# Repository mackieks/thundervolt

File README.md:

<picture> <source media="(prefers-color-scheme: dark)" srcset="images/thundervolt_logo_white.png">  </picture> 

Thundervolt is a suite of open-source hardware and software that enables software-configurable undervolting of 4-layer Wiis. 

The Thundervolt PCBs (Thundervolt 1 and Thundervolt Lite shown) are stylish, highly-integrated power hats for 4-layer Wiis that solder directly to the Wii motherboard. Only 3 wires are necessary to connect Thundervolt to the Wii (I2C and Reset). Power is supplied via two additional wires.

The Thundervolt homebrew app (Dolphin debug version shown) provides granular control over each voltage regulator on the Thundervolt board, as well as emergency overtemperature protection with a configurable threshold. 

Users can apply changes live, and save settings to Thundervolt's EEPROM for persistence across reboots. 

More functionality such as CPU/GPU/MEM stress tests and a power monitor for Thundervolt 2 will be added to the app in the future.

## Features
- 0.8mm 4L rigid PCB — solders directly to 4-layer Wii motherboards
- 55 x 47mm — fits within all but the most extreme trim outlines
- 2.4V to 5.5V input (intended for 1S li-ion or 5V USB-C)
- Highly efficient I2C-controlled buck regulators for 1V, 1.15V, and 1.8V (η > 90%)
- Highly efficient I2C-controlled buck-boost regulator for 3.3V (η > 90%)
- Dynamic undervolting, configurable via Wii homebrew app
- Safe mode solder jumper to force stock voltages
- Wii power-on reset functionality (aka U10 emulation)
- Onboard TMP1075N for temperature monitoring and emergency overtemp shutdown
- Integrated INA700s for realtime voltage/current/power monitoring (Thundervolt 2 only)

## What Thundervolt does NOT do
- Battery management and charging
- Fan control
- Power button handling for portables
- USB PD negotiation

Adding a full BMS to Thundervolt would require major sacrifices to regulator efficiency, thermal performance, and cost. A companion board called *Mjolnir* is in development to fulfill these needs, and will feature tight integration with the existing Thundervolt ecosystem.

## Ordering & Assembly

See [the hardware folder](https://github.com/mackieks/thundervolt/tree/main/hardware) for details on ordering and [assembling](https://github.com/mackieks/thundervolt/blob/main/hardware/ASSEMBLY.md) Thundervolt PCBs.

## Usage
The homebrew app is pretty self explanatory; see [the demo on YouTube](https://youtu.be/DeZFMLoE9EQ) for details. A full writeup will come later.

## Credits

Thundervolt hardware designed by YveltalGriffin

Thundervolt firmware by loopj

Thundervolt homebrew by:
- YveltalGriffin (UI, app)
- loopj (I2C, app)
- Alex/supertazon (graphics)
- ShockSlayer (music)

## License

Thundervolt hardware is licensed under Solderpad Hardware License v2.1.

Thundervolt software (firmware + homebrew) is provided under The MIT License.

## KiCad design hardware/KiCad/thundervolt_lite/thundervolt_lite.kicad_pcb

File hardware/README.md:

<picture> <source media="(prefers-color-scheme: dark)" srcset="../images/thundervolt_logo_white.png">  </picture> 

There are 3 variants of the Thundervolt PCB. As of 2024-07-07, **Thundervolt Lite** and **Thundervolt 1** have been released.
- **Thundervolt Lite**
  - A low cost revision of the original design with **identical functionality** to Thundervolt 1. It does not require VIPPO and only costs $7 for 10 bare boards!
  - Thundervolt Lite is easier to assemble and easier to solder to the Wii motherboard.
  - Fully tested and released to the public! This folder contains the KiCAD source and Gerbers.
- **Thundervolt 1**
  - The original design, with software-controlled undervolting and temperature sensing. It requires a [VIPPO/POFV PCB](https://jlcpcb.com/blog/32-Free-Via-in-Pad-on-6-20-Layer-PCBs-with-POFV) which is rather expensive ($10 per bare board).
  - Fully tested and released to the public! This folder contains the KiCAD source and Gerbers.
- **Thundervolt 2**
  - The Lamborghini of Wii voltage regulation. Thundervolt 2 includes four INA700 power monitor ICs and can report the Wii's current and power consumption in real time. It requires an even higher spec PCB than Thundervolt 1 and is quite expensive ($14-$20 per bare board)
  - Currently unreleased — still in testing

- All Thundervolt revisions require placing and reflowing at least one chipscale BGA (the TPS63810 3.3V buck-boost regulator). 
- Thundervolt 1 and 2 require placing and reflowing an additional chipscale part (LP5907UVX-1.8, 0.7x0.7mm) and have tighter component spacing than Lite. 
- Thundervolt 2 also requires placing four additional chipscale BGAs (INA700, 1.2x1.3mm)
- Thundervolt Lite is the easiest to assemble. Thundervolt 1 is tougher, and Thundervolt 2 is the most challenging. Magnification is highly recommended for assembling all variants.

Two jig PCBs for solderpaste stenciling are also provided. Order both jigs as 2-layer 0.8mm boards.

## Ordering PCBs

### Thundervolt Lite

Recommended board fabrication specs for **Thundervolt Lite** (JLCPCB).

**MANDATORY**
- 0.8mm 4-layer rigid PCB
- Tented or plugged vias
- Min via hole size/diameter: leave at default. Thundervolt Lite has large vias that do not incur additional charges.

Optional
- ENIG (improves solderability for chipscale BGAs)
- 1oz/in² copper on internal layers - not necessary, but technically improves PDN performance (imperceptible to end user)
- Black soldermask - not necessary, but looks great with the lightning bolt art :)

In the **Remark** section of your Thundervolt Lite PCB order, paste the following comment:
```
Kindly note that the graphics on the fMask layer are for aesthetics. Please do NOT edit any of the fMask apertures on the board, or remove any thin soldermask webs. Thank you!
```

If JLC tries to upcharge you for the soldermask artwork, push back. The artwork requires zero additional work or intervention on their part. Feel free to reference my Thundervolt Lite order number if necessary: **Y118-2549677A**

### Thundervolt 1

Recommended board fabrication specs for **Thundervolt 1** (JLCPCB). Thundervolt 1 is a high-spec PCB. Please read this entire section so you understand the fab requirements. 

**MANDATORY**
- 0.8mm 4-layer rigid PCB
- Epoxy Filled & Capped vias (aka VIPPO or POFV)
- Min via hole size/diameter: 0.15mm/(0.25/0.3mm)

Optional
- ENIG (improves solderability for chipscale BGAs)
- 1oz/in² copper on internal layers - not necessary, but technically improves PDN performance (imperceptible to end user)
- Black soldermask - not necessary, but looks great with the lightning bolt art :)

In the **Remark** section of your Thundervolt 1 PCB order, paste the following comment:
```
Kindly note that the graphics on the fMask layer are for aesthetics. Please do NOT edit any of the fMask apertures on the board, or remove any thin soldermask webs. Thank you!
```

If JLC tries to upcharge you for the soldermask artwork, push back. The artwork requires zero additional work or intervention on their part. Feel free to reference my Thundervolt 1 order number if necessary: **Y108-2549677A**

**Note:** Check the box for **Confirm Production File**. Then check the box for "Do Not Confirm Automatically." JLCPCB will often edit the gerbers in unpleasant ways and you **must** push back on this. If they change the via drill sizes, you need to request that they abide by their listed spec of 0.15mm drills. 

A comment like this when reviewing the production file goes a long way:
```
In the production file, the via drill size has been changed from 0.15mm to 0.2mm [or whatever they changed it to]. Please do not change the via size. They should be 0.15mm drill and 0.3mm diameter as in the original file. I greatly appreciate your assistance with this. Thanks!
```

Some amount of "compensation" (growth of annular rings + padshaving) is unavoidable; however, if the drills are increased to 0.2mm or more, this will result in extreme padshaving of many vias/traces. You'll also notice that they expand the copper clearance around drills on inner layers as part of the compensation process. As long as they are not changing the drill diameters, this is OK. They may also request to remove annular rings ("pads") on internal layers. This is OK as it lessens the impact of their copper clearance expansion on the inner planes.

## Stencil and Jig

Both an electropolished solder paste stencil and the two jig PCBs (jig1, jig2) are **highly** recommended for assembly. 

**MANDATORY STENCIL SPECS**
- Custom dimensions: **90 x 90mm**
- Top only
- Electropolishing

Order both jig1 and jig2 as 0.8mm 2-layer PCBs. In the **Remark** section of both jig PCB orders, paste the following comment:
```
Please note that this is a mechanical PCB and does not contain any drill holes or soldermask openings. Thank you!
```

## BOM

**Thundervolt Lite:** [Link to Mouser cart with BOM](https://www.mouser.com/ProjectManager/ProjectDetail.aspx?AccessID=3CC491924A) [Link to Digikey cart with BOM](https://www.digikey.com/en/mylists/list/P9BJON8540)

**Thundervolt 1**: [Link to Mouser cart with BOM](https://www.mouser.com/ProjectManager/ProjectDetail.aspx?AccessID=D2F0182832)

**Note:** The 0412CDMCCDS-R22MC low-profile inductors used on Thundervolt Lite are only available [from Digikey.](https://www.digikey.com/en/products/detail/sumida-america-inc/0412CDMCCDS-R22MC/11682034)

**Note:** The XFL5015-221MEC low-profile inductors used on Thundervolt 1 and Thundervolt 2 are only available [directly from Coilcraft.](https://www.coilcraft.com/en-us/products/power/shielded-inductors/molded-inductor/xfl/xfl501x/xfl5015-221/)

## Assembly

See [ASSEMBLY.md](https://github.com/mackieks/thundervolt/blob/main/hardware/ASSEMBLY.md) for assembly instructions.

## License

Thundervolt hardware was designed by YveltalGriffin and is licensed under Solderpad Hardware License v2.1.

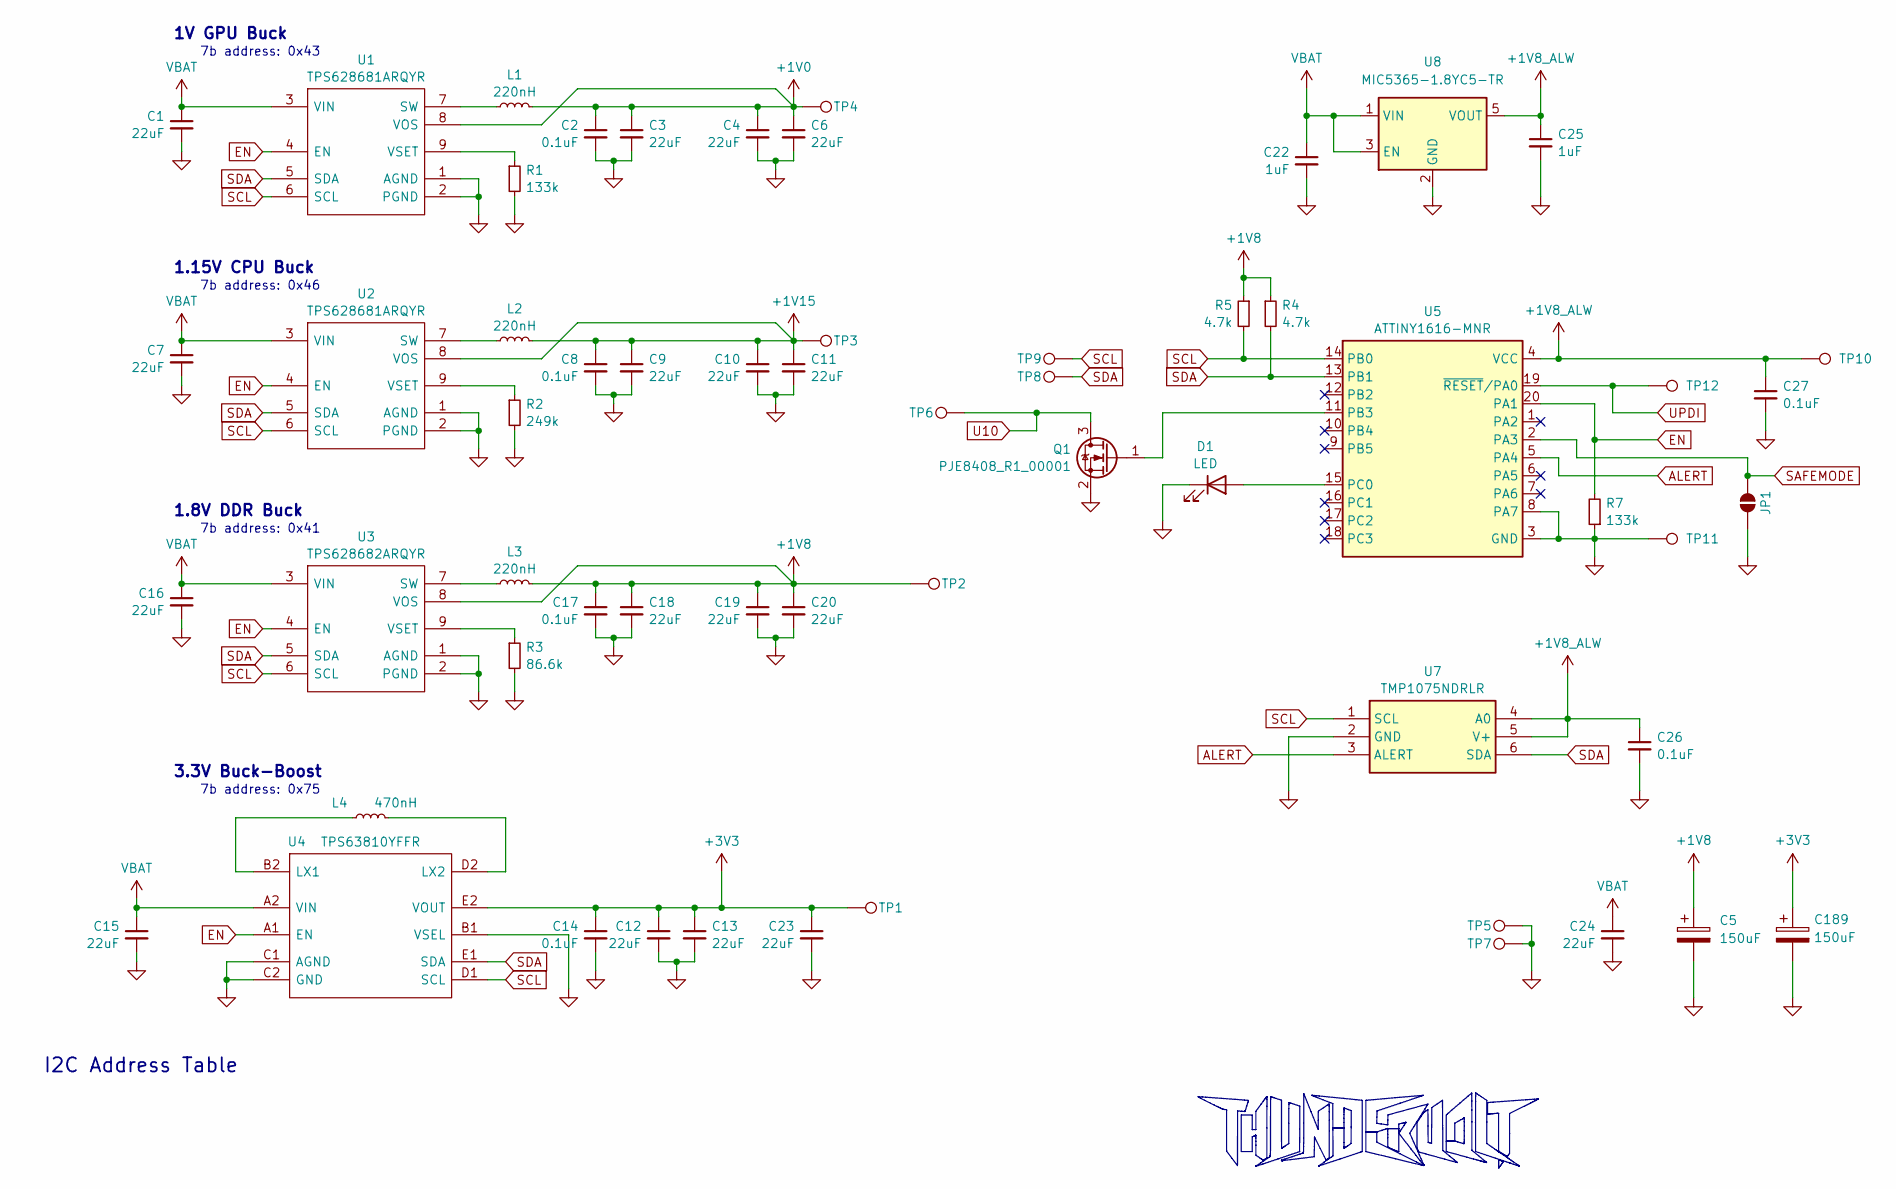
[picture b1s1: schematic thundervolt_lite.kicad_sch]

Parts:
C1, C3, C4, C6, C7, C9, C10, C11, C12, C13, C15, C16, C18, C19, C20, C23, C24: 22uF; C_0603_1608Metric
C2, C8, C14, C17, C26, C27: 0.1uF; C_0402_1005Metric
C5, C189: 150uF; CP_EIA-3528-15_AVX-H
C22, C25: 1uF; C_0402_1005Metric
D1: LED; LED_0603_1608Metric
JP1: SolderJumper_2_Open; SolderJumper-2_P1.3mm_Open_RoundedPad1.0x1.5mm
L1, L2: 220nH; 0412CDMCCDS-R22MC
L3: 220nH; INDC3225X120N
L4: 470nH; L_0805_2012Metric
Q1: PJE8408_R1_00001; SOT-523
R1, R7: 133k; R_0402_1005Metric
R2: 249k; R_0402_1005Metric
R3: 86.6k; R_0402_1005Metric
R4, R5: 4.7k; R_0402_1005Metric
TP1: 3V3; TestPoint_Pad_1.5x1.0mm
TP2: 1V8; TestPoint_Pad_3x1.0mm
TP3: 1V15; TestPoint_Pad_3x1.0mm
TP4: 1V0; TestPoint_Pad_3x1.0mm
TP5, TP7: GND; TestPoint_Pad_3x1.0mm
TP6, TP8: SDA; TestPoint_Pad_D1.0mm
TP9: SCL; TestPoint_Pad_D1.0mm
TP10: VBAT; TestPoint_Pad_D1.0mm
TP11: GND; TestPoint_Pad_D1.0mm
TP12: UPDI; TestPoint_Pad_D1.0mm
U1, U2: TPS628681ARQYR; TPS628680ARQYR; Mouser Part Number 595-TPS628680ARQYR
U3: TPS628682ARQYR; TPS628680ARQYR; Mouser Part Number 595-TPS628680ARQYR
U4: TPS63810YFFR; BGA15C40P3X5_134X226X62; Mouser Part Number 595-TPS63810YFFR
U5: ATTINY1616-MNR; VQFN-20-1EP_3x3mm_P0.4mm_EP1.7x1.7mm
U7: TMP1075NDRLR; SOTFL50P160X60-6N; Mouser Part Number 595-TMP1075NDRLR
U8: MIC5365-1.8YC5-TR; SOT-353_SC-70-5

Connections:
+1V0: C2.1, C3.1, C4.1, C6.1, L1.2, TP4.1, U1.8 (VOS)
+1V8: C5.1, C17.1, C18.1, C19.1, C20.1, L3.2, R4.1, R5.1, TP2.1, U3.8 (VOS)
+1V8_ALW: C25.1, C26.1, C27.1, TP10.1, U5.4 (VCC), U7.4 (A0), U7.5 (V+), U8.5 (VOUT)
+1V15: C8.1, C9.1, C10.1, C11.1, L2.2, TP3.1, U2.8 (VOS)
+3V3: C12.1, C13.1, C14.1, C23.1, C189.1, TP1.1, U4.E2 (VOUT), U4.E3 (VOUT_2)
ALERT: U5.5 (PA4), U7.3 (ALERT)
EN: R7.2, U1.4 (EN), U2.4 (EN), U3.4 (EN), U4.A1 (EN), U5.20 (PA1)
GND: C1.2, C2.2, C3.2, C4.2, C5.2, C6.2, C7.2, C8.2, C9.2, C10.2, C11.2, C12.2, C13.2, C14.2, C15.2, C16.2, C17.2, C18.2, C19.2, C20.2, C22.2, C23.2, C24.2, C25.2, C26.2, C27.2, C189.2, D1.1 (K), JP1.1 (A), Q1.2 (S), R1.2, R2.2, R3.2, R7.1, TP5.1, TP7.1, TP11.1, U1.1 (AGND), U1.2 (PGND), U2.1 (AGND), U2.2 (PGND), U3.1 (AGND), U3.2 (PGND), U4.B1 (VSEL), U4.C1 (AGND), U4.C2 (GND), U4.C3 (GND_2), U5.3 (GND), U5.8 (PA7), U5.21 (GND), U7.2 (GND), U8.2 (GND)
unnamed: D1.2 (A), U5.15 (PC0)
unnamed: Q1.1 (G), U5.11 (PB3)
unnamed: L1.1, U1.7 (SW)
unnamed: R1.1, U1.9 (VSET)
unnamed: L2.1, U2.7 (SW)
unnamed: R2.1, U2.9 (VSET)
unnamed: L3.1, U3.7 (SW)
unnamed: R3.1, U3.9 (VSET)
unnamed: L4.1, U4.B2 (LX1), U4.B3 (LX1_2)
unnamed: L4.2, U4.D2 (LX2), U4.D3 (LX2_2)
SAFEMODE: JP1.2 (B), U5.2 (PA3)
SCL: R5.2, TP9.1, U1.6 (SCL), U2.6 (SCL), U3.6 (SCL), U4.D1 (SCL), U5.14 (PB0), U7.1 (SCL)
SDA: R4.2, TP8.1, U1.5 (SDA), U2.5 (SDA), U3.5 (SDA), U4.E1 (SDA), U5.13 (PB1), U7.6 (SDA)
U10: Q1.3 (D), TP6.1
UPDI: TP12.1, U5.19 (~RESET/PA0)
VBAT: C1.1, C7.1, C15.1, C16.1, C22.1, C24.1, U1.3 (VIN), U2.3 (VIN), U3.3 (VIN), U4.A2 (VIN), U4.A3 (VIN_2), U8.1 (VIN), U8.3 (EN)

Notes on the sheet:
I2C Address Table
3.3V Buck-Boost
1.15V CPU Buck
7b address: 0x43
7b address: 0x41
1.8V DDR Buck
1V GPU Buck
7b address: 0x75
7b address: 0x46

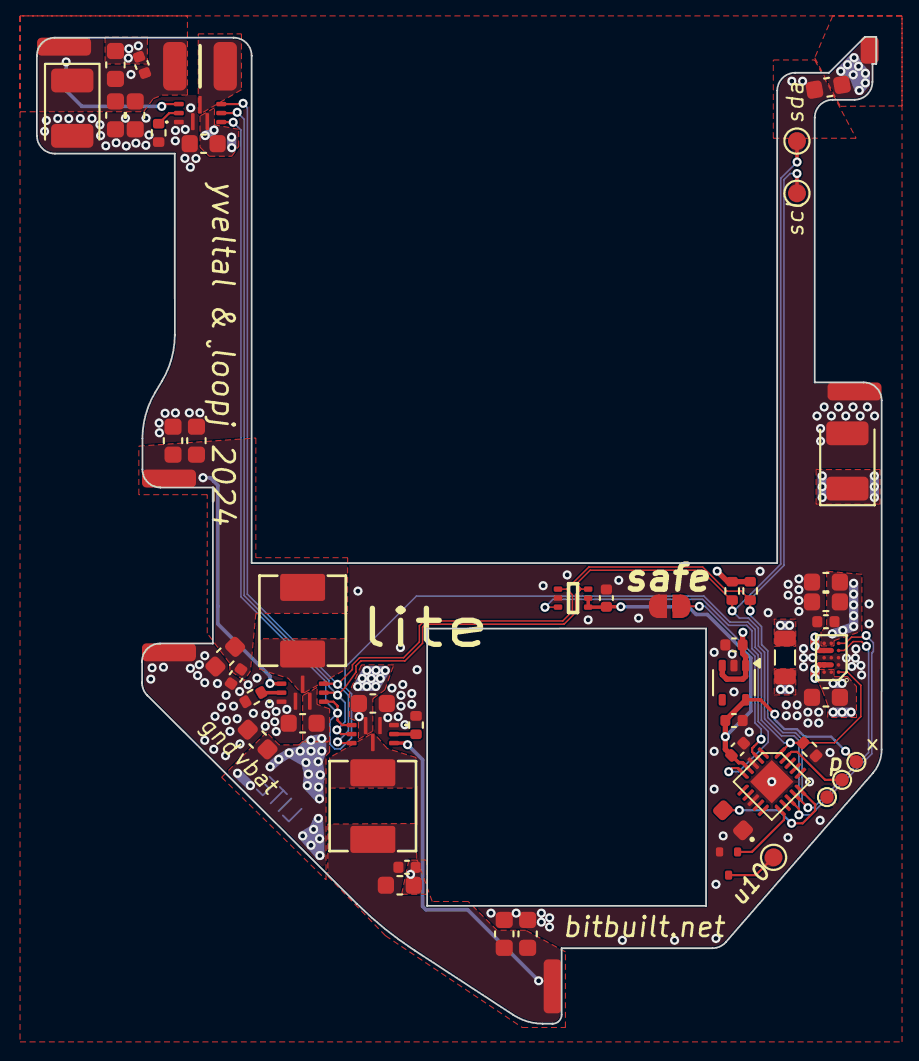
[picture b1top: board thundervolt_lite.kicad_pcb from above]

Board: 13 copper layers, 46.9 x 54.8 mm, 59 parts (0 on the bottom side), 24 nets.

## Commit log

2024-07-01 Update releases link
2024-07-04 Remove HW2 gerbers and update HW1 gerbers
2024-07-04 Update gerbers
2024-07-04 Update hardware filenames
2024-07-08 Add Thundervolt Lite hardware files
2024-07-08 update board img
2024-07-15 Add assembly images
2024-09-05 U10 FET Mode
2024-09-05 Update lite gerbers
2024-12-09 Fix occasional EEPROM write failures
2025-03-04 reg detection
2025-03-10 Add power-on self test scan
2025-09-15 Add more detail around i2c bitbang implementation, Zephyr license
2026-02-06 Thundervolt 2 support (WIP)
2026-04-20 Fix reset SYS_SetResetCallback prototype
